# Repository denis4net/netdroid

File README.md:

netdroid
========

NetDroid project:
	NetDroid is neuraxis for RC robot.

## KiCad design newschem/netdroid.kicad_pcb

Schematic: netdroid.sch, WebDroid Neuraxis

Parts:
8MHz1: CRYSTAL
ADC1, ADC2: CONN_2
C1, C4, C5, C6, C7: 100nF
C2, C3: 20pF
C9: 1uF
D11, D12, D13, D14, D21, D22, D23, D24, D31, D32, D33, D34, D41, D42, D43, D44: DIODE
ENG1, ENG2, ENG3, ENG4: engpin
JP_BOOT0, JP_BOOT1: BREAKER
KEY1, KEY2, KEY3, KEY4: IR4426
LED1, LED2: LED
P1, P2, P3, P4, P5, P6, P7, P8: CONN_1
PSWD1: CONN_2
PWR1: CONN_2
PWR2: CONN_3
R1: 330
R2, R3: 10k
R4, R5: 510
R6, R7: R
SERVO1: CONN_4
U1: STM32F100C4; LQFP48
USART1, USART2: CONN_2
reset1: SW_PUSH

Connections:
+12V: D11.2 (K), D13.2 (K), D21.2 (K), D23.2 (K), D31.2 (K), D33.2 (K), D41.2 (K), D43.2 (K), KEY1.6 (Vs), KEY2.6 (Vs), KEY3.6 (Vs), KEY4.6 (Vs), P6.1, P7.1, PWR2.3
unnamed: KEY2.4 (INB), U1.42 (PB6/I2C1_SCL/TIM16_CH1N)
unnamed: KEY1.4 (INB), U1.45 (PB8/TIM4_CH3/TIM16_CH1/CEC)
unnamed: KEY1.2 (INA), U1.46 (PB9/TIM4_CH4/TIM17_CH1)
unnamed: JP_BOOT1.1, R3.1, U1.20 (PB2/BOOT1)
unnamed: KEY4.2 (INA), U1.17 (SPI1_MOSI/ADC1_IN7/TIM3_CH2/PA7)
unnamed: KEY4.4 (INB), U1.16 (SPI1_MISO/ADC1_IN6/TIM3_CH1/PA6)
unnamed: C1.1, R1.1, U1.7 (~NRST), reset1.2
unnamed: JP_BOOT0.1, R2.1, U1.44 (BOOT0)
unnamed: SERVO1.1, U1.28 (PB15/TIM1_CH3N/TIM15_CH1N)
unnamed: SERVO1.4, U1.25 (PB12/TIM1_BKIN)
unnamed: SERVO1.3, U1.26 (PB13/TIM1_CH1N)
unnamed: SERVO1.2, U1.27 (PB14/TIM1_CH2N)
unnamed: U1.13 (USART2_RX/ADC1_IN3/TIM2_CH4/TIM15_CH2/P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), USART2.2 (PM)
unnamed: U1.12 (USART2_TX/ADC1_IN2/TIM2_CH3/TIM15_CH1/P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), USART2.1
unnamed: KEY3.4 (INB), U1.18 (PB0/ADC1_IN8/TIM3_CH3)
unnamed: KEY3.2 (INA), U1.19 (PB1/ADC1_IN9/TIM3_CH4)
unnamed: ADC1.2 (PM), U1.10 (WKUP/USART2_CTS/ADC1_IN0/TIM2_CH1_ETR/P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)
unnamed: ADC2.2 (PM), U1.11 (USART2_RTS/ADC1_IN1/TIM2_CH2/PA1)
unnamed: KEY2.2 (INA), U1.43 (PB7/I2C1_SDA/TIM17_CH1N)
unnamed: PSWD1.2 (PM), U1.37 (JTCK/SWCLK/PA14)
unnamed: U1.31 (USART1_RX/TIM1_CH3/TIM17_BKIN/PA10), USART1.2 (PM)
unnamed: U1.30 (USART1_TX/TIM1_CH2/TIM15_BKIN/PA9), USART1.1
unnamed: PSWD1.1, U1.34 (JTMS/SWDIO/PA13)
unnamed: JP_BOOT0.2, R4.1
unnamed: JP_BOOT1.2, R5.1
unnamed: 8MHz1.2, C3.2, U1.6 (OSC_OUT)
unnamed: D43.1 (A), D44.2 (K), ENG4.2 (PM), KEY4.5 (OUTB)
unnamed: D11.1 (A), D12.2 (K), ENG1.1, KEY1.7 (OUTA)
unnamed: D13.1 (A), D14.2 (K), ENG1.2 (PM), KEY1.5 (OUTB)
unnamed: D41.1 (A), D42.2 (K), ENG4.1, KEY4.7 (OUTA)
unnamed: LED1.1 (A), R6.2
unnamed: D21.1 (A), D22.2 (K), ENG2.1, KEY2.7 (OUTA)
unnamed: D23.1 (A), D24.2 (K), ENG2.2 (PM), KEY2.5 (OUTB)
unnamed: D31.1 (A), D32.2 (K), ENG3.1, KEY3.7 (OUTA)
unnamed: 8MHz1.1, C2.1, U1.5 (OSC_IN)
unnamed: D33.1 (A), D34.2 (K), ENG3.2 (PM), KEY3.5 (OUTB)
unnamed: LED2.1 (A), R7.2
VDD: C4.2, C5.2, C6.2, C7.2, C9.2, P1.1, P2.1, P3.1, P4.1, P5.1, PWR1.2 (PM), PWR2.2 (PM), R1.2, R2.2, R3.2, R6.1, U1.9 (VDDA), U1.24 (VDD), U1.36 (VDD), U1.48 (VDD), reset1.1
VSS: ADC1.1, ADC2.1, C1.2, C2.2, C3.1, C4.1, C5.1, C6.1, C7.1, C9.1, D12.1 (A), D14.1 (A), D22.1 (A), D24.1 (A), D32.1 (A), D34.1 (A), D42.1 (A), D44.1 (A), KEY1.3 (GND), KEY2.3 (GND), KEY3.3 (GND), KEY4.3 (GND), LED1.2 (K), LED2.2 (K), P8.1, PWR1.1, PWR2.1, R4.2, R5.2, U1.8 (VSSA), U1.23 (VSS), U1.35 (VSS), U1.47 (VSS)

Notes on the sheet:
service\dbg 115200 8N1 uart

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
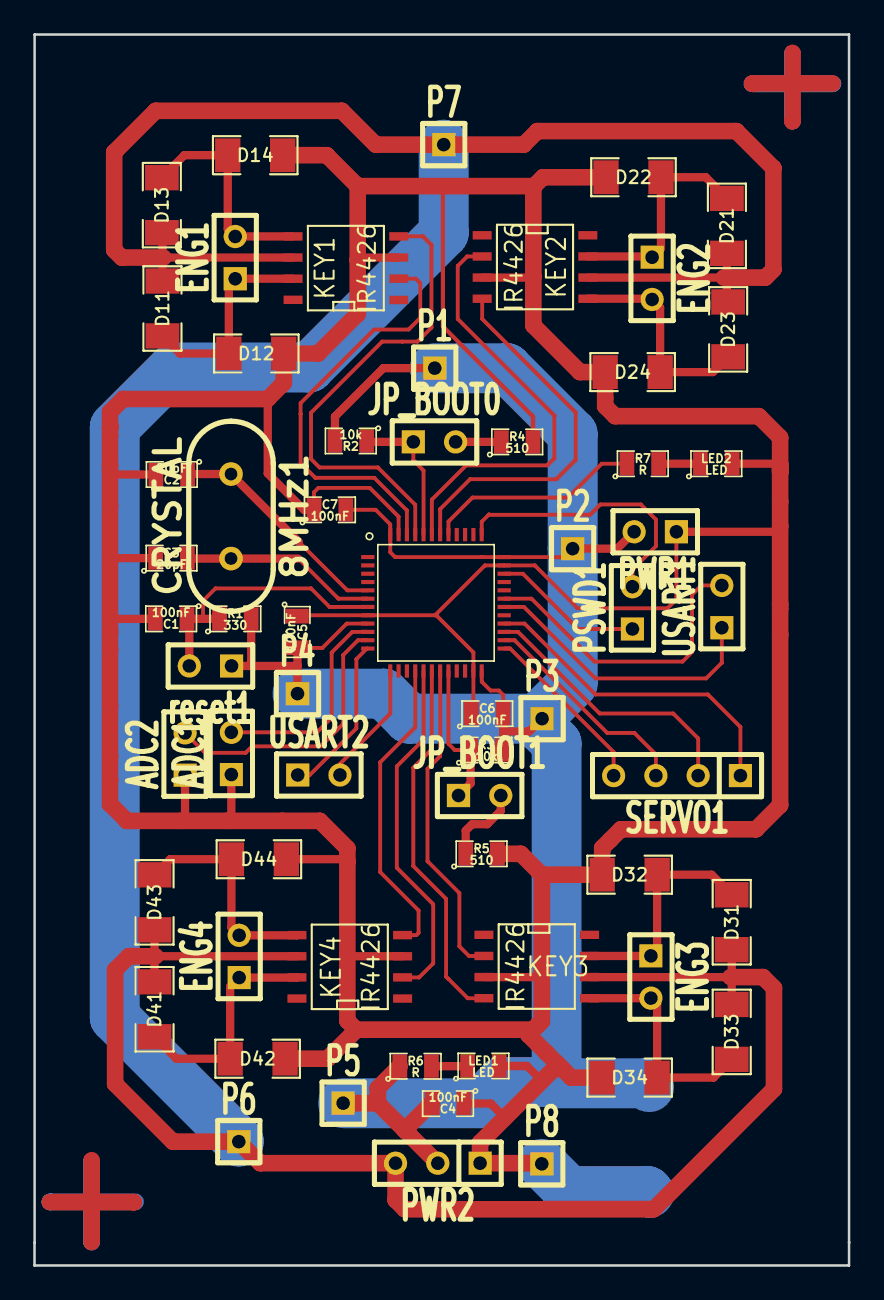
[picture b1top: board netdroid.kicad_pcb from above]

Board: 2 copper layers, 49.0 x 74.0 mm, 62 parts (1 on the bottom side), 41 nets.

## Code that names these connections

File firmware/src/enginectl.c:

/**
 * @file enginectl.c
 * @author Denis Vashchuk
 * @brief Implementation of PWM engines control
 * @copyright BSUIR 2013
 *
 * <h2>Engines placement on a board.</h2>
 * @image html ../../images/neuraxis_pwm.png
 */

 /*
 * Channel (Forward)	|		Channel (Back)	|	Engine #	|	Description
 * _________________|_______________________|_______________|______________
 * TIM4_CH1 (PB6)	|	 	TIM4_CH2 (PB7)	|	 	ENG1	|	Front left
 * TIM4_CH3 (PB8)	|		TIM4_CH4 (PB9)	|		ENG2	|	Front right
 * TIM3_CH1 (PA6)	|		TIM3_CH2 (PA7)	|		ENG3	|	Back right
 * TIM3_CH3 (PB0)	|		TIM3_CH4 (PB1)	|		ENG4	|	Back left
 *
 */


#include "enginectl.h"
#include "led.h"
#include <stm32f10x_tim.h>

#define PWM_PERIOD 100
#define ENGINE_SPEED(x) (x-1)
#define ENGINE_STOP	0



extern void delay(uint32_t ms);

/**
 * @brief Init GPIO, PWM for engines control
 */
void engine_init()
{

	RCC_APB1PeriphClockCmd(RCC_APB1Periph_TIM3, ENABLE);
	RCC_APB1PeriphClockCmd(RCC_APB1Periph_TIM4, ENABLE);
	RCC_APB2PeriphClockCmd(RCC_APB2Periph_GPIOA, ENABLE);
	RCC_APB2PeriphClockCmd(RCC_APB2Periph_GPIOB, ENABLE);

	/* Enable gpio pins for engine */
	GPIO_InitTypeDef gpio_a;
	gpio_a.GPIO_Mode = GPIO_Mode_AF_PP;
	gpio_a.GPIO_Pin = GPIO_Pin_6 | GPIO_Pin_7;
	gpio_a.GPIO_Speed = GPIO_Speed_2MHz;
	GPIO_Init(GPIOA, &gpio_a);

	GPIO_InitTypeDef gpio_b;
	gpio_b.GPIO_Mode = GPIO_Mode_AF_PP;
	gpio_b.GPIO_Pin = GPIO_Pin_0 | GPIO_Pin_1 | GPIO_Pin_6 | GPIO_Pin_7 | GPIO_Pin_8 | GPIO_Pin_9;
	gpio_b.GPIO_Speed = GPIO_Speed_2MHz;
	GPIO_Init(GPIOB, &gpio_b);

	/* timers */
	TIM_TimeBaseInitTypeDef timer_config;
	timer_config.TIM_CounterMode=TIM_CounterMode_Up;
	timer_config.TIM_ClockDivision=0;
	timer_config.TIM_Prescaler = 0;
	timer_config.TIM_Period = PWM_PERIOD-1;

	TIM_TimeBaseInit(TIM3, &timer_config);
	TIM_TimeBaseInit(TIM4, &timer_config);

	TIM_OCInitTypeDef timer_oconfig;
	timer_oconfig.TIM_OCMode = TIM_OCMode_PWM1;
	timer_oconfig.TIM_OutputState = TIM_OutputState_Enable;
	timer_oconfig.TIM_Pulse = ENGINE_STOP;
	timer_oconfig.TIM_OCPolarity = TIM_OCPolarity_High;

	//Timer 3
	TIM_OC1Init(TIM3, &timer_oconfig);
	TIM_OC2Init(TIM3, &timer_oconfig);
	TIM_OC3Init(TIM3, &timer_oconfig);
	TIM_OC4Init(TIM3, &timer_oconfig);
	//Timer 4
	TIM_OC1Init(TIM4, &timer_oconfig);
	TIM_OC2Init(TIM4, &timer_oconfig);
	TIM_OC3Init(TIM4, &timer_oconfig);
	TIM_OC4Init(TIM4, &timer_oconfig);

	TIM_OC1PreloadConfig(TIM3, TIM_OCPreload_Enable);
	TIM_OC2PreloadConfig(TIM3, TIM_OCPreload_Enable);
	TIM_OC3PreloadConfig(TIM3, TIM_OCPreload_Enable);
	TIM_OC4PreloadConfig(TIM3, TIM_OCPreload_Enable);

	TIM_OC1PreloadConfig(TIM3, TIM_OCPreload_Enable);
	TIM_OC2PreloadConfig(TIM3, TIM_OCPreload_Enable);
	TIM_OC3PreloadConfig(TIM3, TIM_OCPreload_Enable);
	TIM_OC4PreloadConfig(TIM3, TIM_OCPreload_Enable);

	TIM_ARRPreloadConfig(TIM3, ENABLE);
	TIM_ARRPreloadConfig(TIM4, ENABLE);

	TIM_Cmd(TIM3, ENABLE);
	TIM_Cmd(TIM4, ENABLE);
}

/**
 * All function engine_go_* and engine_turn_* are blocking
 */

/**
 * @brief Power on engine to drive forward
 * @param time time in ms
 * @param speed_value max value PWM_PERIOD
 */
void engine_go_forward(int time_ms, int speed_value)
{
	TIM3->CCR1 = ENGINE_SPEED(speed_value);
	TIM3->CCR3 = ENGINE_SPEED(speed_value);
	TIM4->CCR1 = ENGINE_SPEED(speed_value);
	TIM4->CCR3 = ENGINE_SPEED(speed_value);

	led_delay(time_ms);

	engine_stop();
}


/**
 * @brief Power on engine to drive backward
 * @param time time in ms
 * @param speed_value max value PWM_PERIOD
 */
void engine_go_backward(int time_ms, int speed_value)
{
	TIM3->CCR2 = ENGINE_SPEED(speed_value);
	TIM3->CCR4 = ENGINE_SPEED(speed_value);
	TIM4->CCR2 = ENGINE_SPEED(speed_value);
	TIM4->CCR4 = ENGINE_SPEED(speed_value);
	led_delay(time_ms);

	engine_stop();
}


/**
 * @brief Power on engine to drive forward while command engine_stop not be executed
 * @param speed_value max value PWM_PERIOD
 */
void engine_go_forward_continuously(int speed_value)
{
	TIM3->CCR1 = ENGINE_SPEED(speed_value);
	TIM3->CCR3 = ENGINE_SPEED(speed_value);
	TIM4->CCR1 = ENGINE_SPEED(speed_value);
	TIM4->CCR3 = ENGINE_SPEED(speed_value);
}

/**
 * @brief Stop all engines
 */
void engine_stop()
{
	TIM3->CCR1 = ENGINE_STOP;
	TIM3->CCR2 = ENGINE_STOP;
	TIM3->CCR3 = ENGINE_STOP;
	TIM3->CCR4 = ENGINE_STOP;

	TIM4->CCR1 = ENGINE_STOP;
	TIM4->CCR2 = ENGINE_STOP;
	TIM4->CCR3 = ENGINE_STOP;
	TIM4->CCR4 = ENGINE_STOP;
}

/**
 * @brief Turn right (direction: forward)
 */
void engine_turn_right_forward(int angle)
{
	TIM3->CCR2 = ENGINE_SPEED(100);
	TIM4->CCR4 = ENGINE_SPEED(100);

	TIM3->CCR3 = ENGINE_SPEED(100);
	TIM4->CCR1 = ENGINE_SPEED(100);
	led_delay(angle);
	engine_stop();
}

/**
 * @brief Turn left (direction: forward)
 */
void engine_turn_left_forward(int angle)
{
	TIM3->CCR4 = ENGINE_SPEED(100);
	TIM4->CCR2 = ENGINE_SPEED(100);

	TIM3->CCR1 = ENGINE_SPEED(100);
	TIM4->CCR3 = ENGINE_SPEED(100);
	led_delay(angle);
	engine_stop();
}


/**
 * @brief Turn right (direction: backward)
 */
void engine_turn_right_backward(int angle)
{
	TIM3->CCR4 = ENGINE_SPEED(100);
	TIM4->CCR2 = ENGINE_SPEED(100);

	TIM3->CCR1 = ENGINE_SPEED(100);
	TIM4->CCR3 = ENGINE_SPEED(100);
	led_delay(angle);
	engine_stop();
}

/**
 * @brief Turn left (direction: backward)
 */
void engine_turn_left_backward(int angle)
{
	TIM3->CCR2 = ENGINE_SPEED(100);
	TIM4->CCR4 = ENGINE_SPEED(100);

	TIM3->CCR3 = ENGINE_SPEED(100);
	TIM4->CCR1 = ENGINE_SPEED(100);
	led_delay(angle);
	engine_stop();
}

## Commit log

2013-09-15 Base source tree added
2013-09-15 Documentation added
2013-09-16 Makefile optimized
2013-09-27 Shell skeleton. UART1->UART2
2013-09-28 Schem improved: 4 engines, 2 servo out added
2013-09-29 Keys added
2013-10-22 Переделана заново схема, исправлена куча ошибок
2013-11-07 почти нарисовал схкму. Не нашел переходные отверстия. Заебало.
2013-11-07 USART2 irq implementation
2013-11-08 Shell implemented. Command queue added. Help command implemented. String embedded library added
2013-11-09 Moving to Eclipse. STD lib and argument parsing added
2013-11-11 захуярил схему
2013-11-12 вроде все
2013-11-14 PWM Fixies
2013-11-16 Надеюсь, это финальная версия
2013-11-20 заел на будущее
2013-11-26 implemented commands handler for turn commands
2013-12-01 PWM init/control implemented
2013-12-14 Build system fixes
2013-12-14 Project rename
2014-02-09 Release 1.0
2014-03-15 UART Shell bug fixed
2014-03-15 Repo ranked
